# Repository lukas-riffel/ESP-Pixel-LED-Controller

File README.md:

# ESP-Pixel-LED-Controller
An open source Pixel-LED-Decoder based on WT32-ETH01 using WLED with usermods.

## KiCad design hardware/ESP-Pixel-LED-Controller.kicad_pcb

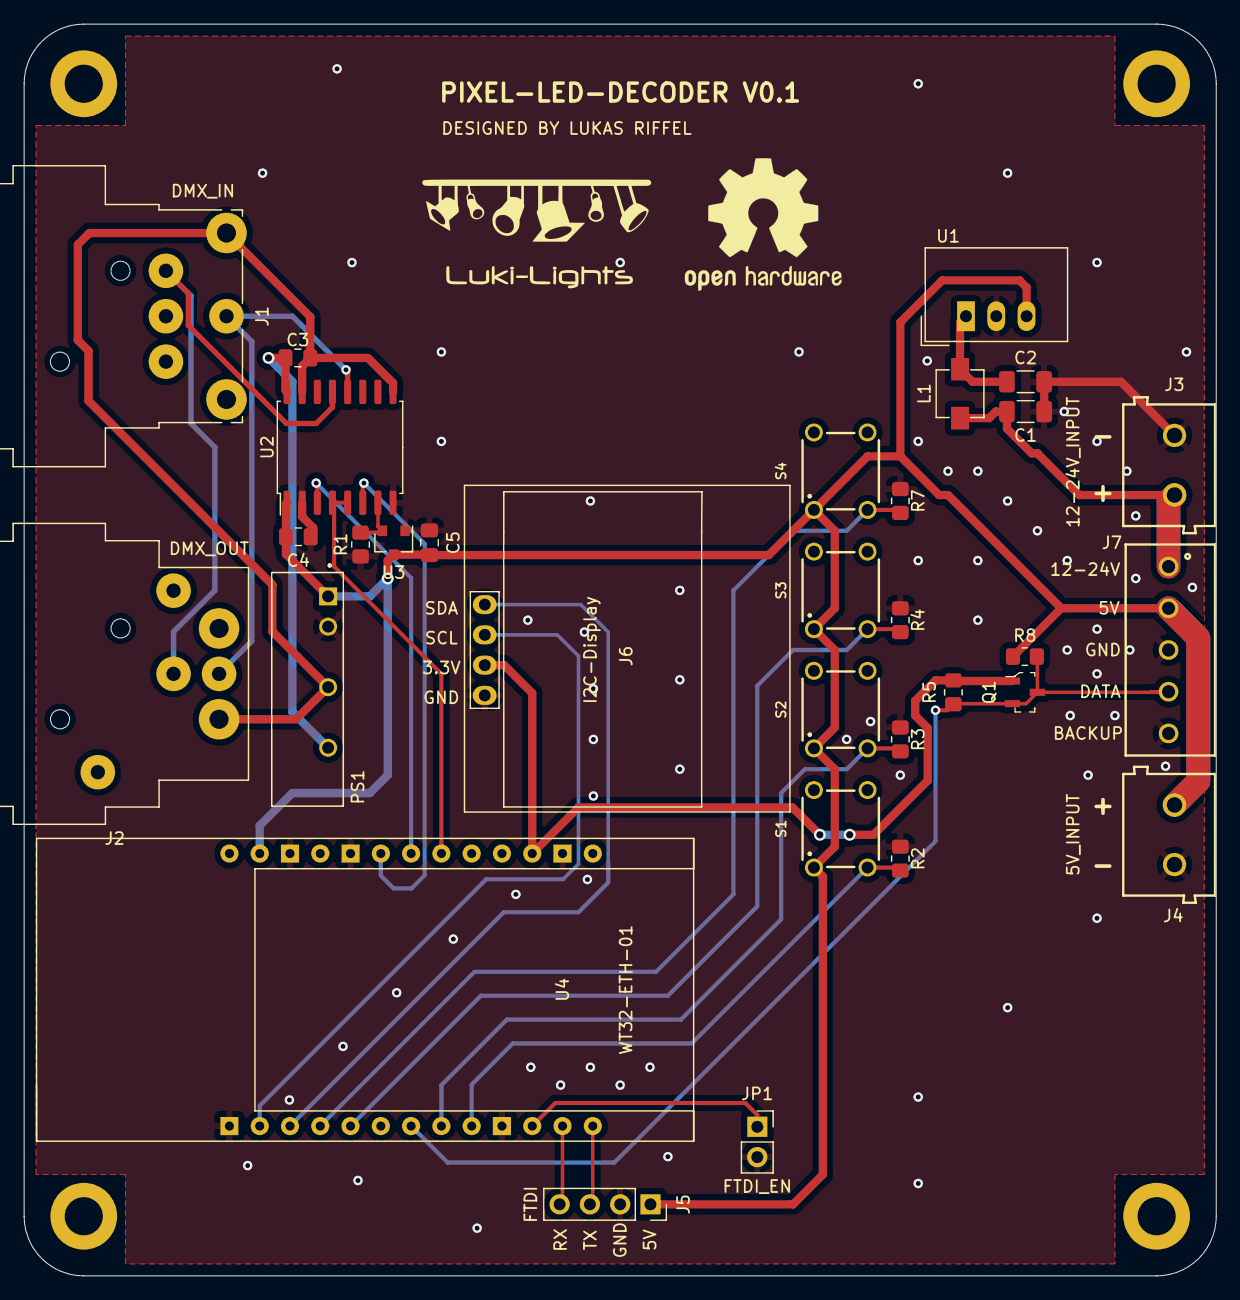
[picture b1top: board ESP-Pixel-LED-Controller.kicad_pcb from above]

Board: 2 copper layers, 100.0 x 105.0 mm, 31 parts (0 on the bottom side), 23 nets.

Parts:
C1, C2: 10uF; C_1206_3216Metric_Pad1.33x1.80mm_HandSolder
C3, C4, C5: 100nF; C_0805_2012Metric_Pad1.18x1.45mm_HandSolder
J1: DMX_IN; Jack_XLR_Neutrik_NC5MBH-B_Horizontal
J2: DMX_OUT; Jack_XLR_Neutrik_NC5FBH-B_Horizontal
J3: 12V INPUT; 691102710002
J4: 5V INPUT; 691102710002
J5: FTDI; PinSocket_1x04_P2.54mm_Vertical
J6: I2C-Display; 128x64OLED
J7: LED-Stripe; 691243110005
JP1: FTDI_EN; PinSocket_1x02_P2.54mm_Vertical
L1: 5,6uH TCK141; TCK-141
PS1: REE-0505S; CONV_REE-0505S
Q1: BSS138; SOT-23-3
R1: 100K; R_0805_2012Metric_Pad1.20x1.40mm_HandSolder
R2, R3, R4, R5, R7, R8: 10K; R_0805_2012Metric_Pad1.20x1.40mm_HandSolder
S1, S2, S3, S4: 430156095726; WE_4301X60957X6
U1: TSR_1-2450; Converter_DCDC_TRACO_TSR-1_THT
U2: ADM2483xRW; SOIC-16W_7.5x10.3mm_P1.27mm
U3: LM809; SOT-23
U4: WT32-ETH-01; WT32_ETH01

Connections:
+3V3: J6.3, Q1.1 (G), R5.2, U4.3 (3V3)
+5V: C4.2, C5.1, J4.2, J5.1, J7.2, PS1.1 (+VIN), R8.2, S1.1, S2.1, S3.1, S4.1, U1.3 (Vout), U2.1 (VDD1), U3.3 (VCC), U4.12 (5V)
+5VD: C3.2, PS1.6 (+VOUT), U2.16 (VDD2)
+12V: C1.2, J3.2, J7.1, L1.2
/+DMX: J1.3, J2.3, U2.12 (A)
/-DMX: J1.2, J2.2, U2.13 (B)
/DATA_LED: J7.4, Q1.2 (S), Q1.3 (D), R5.1, R8.1, U4.20 (IO15~)
/EN_485: U2.4 (~RE), U2.5 (DE), U4.6 (485_EN)
/EN_FTDI: JP1.1 (A), U4.16 (IO0~)
/Power_Valid: R1.2, U2.7 (PV), U3.2 (~RESET)
/RX_485: U2.3 (RxD), U4.7 (RXD2_IO5)
/RX_FTDI: J5.4, U4.15 (RXD~)
/SCL: J6.2, U4.25 (IO2)
/SDA: J6.1, U4.24 (IO4)
/TX_485: U2.6 (TxD), U4.8 (TXD2_IO17)
/TX_FTDI: J5.3, U4.14 (TXD)
GND: C1.1, C2.1, C4.1, C5.2, J3.1, J4.1, J5.2, J6.4, J7.3, J7.5, JP1.2 (B), PS1.2 (-VIN), R1.1, R2.1, R3.1, R4.1, R7.1, U1.2 (GND), U2.2 (GND1), U2.8 (GND1), U3.1 (GND), U4.2 (GND~), U4.9 (GND), U4.11 (GND), U4.17 (GND), U4.26 (GND)
GND2: C3.1, J1.1, J2.1, PS1.4 (-VOUT), U2.9 (GND2), U2.15 (GND2)
unnamed: C2.2, L1.1, U1.1 (Vin)
SW_1: R2.2, S1.2, U4.18 (IO39_INPUT~)
SW_2: R3.2, S2.2, U4.19 (IO36_INPUT~)
SW_3: R4.2, S3.2, U4.22 (IO12~)
SW_4: R7.2, S4.2, U4.23 (IO35_INPUT)

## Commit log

2022-06-29 ✨ added .gitignore for KiCad
2022-06-29 🎉 initially added hardware files
2022-06-29 🐛✨ added missing connection
